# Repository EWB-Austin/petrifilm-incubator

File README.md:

# The Armadillo v1.0, a Low-cost, Portable, Petrifilm Incubator

The Armadillo v1.0 is a low-cost, portable Petrifilm(TM) Incubator for doing in-country bacterial analysis of water quality for Engineers Without Borders invented and engineered by the Instrumentation Group of [Great Austin Chapter](https://ewbgreateraustin.org/) of [EWB-USA](http://www.ewb-usa.org/).

Watch a 3-minute introductory [video](https://www.youtube.com/watch?v=0SzoYT8wLo0)!

The Armadillo won [1st place](https://ewbgreateraustin.org/2016/11/01/test/) in in the 2016 SCSE Regional Conference in Atlanta poster session contest.
As we like to say, "we beat NASA", with our [poster](https://github.com/EWB-Austin/petrifilm-incubator/blob/master/doc/EWBconferenceposterIncubator_handout_comp.pdf):

.

## Start Here: Documentation

We have a press release in progress which is not yet published.

Our [instructable](http://www.instructables.com/id/Portable-Petrifilm-Incubator-for-Inexpensive-In-Fi/)
gives step-by-step instructions for the construction of the Armadillo for about $160.

For those who prefer printable and sharable PDF, we have prepared a [construction manual](https://github.com/EWB-Austin/petrifilm-incubator/blob/master/doc/ConstructionManual.pdf).

Because the use of the Armadillo requires inoculating Petrifilms, we have prepared an
[inoculation manual](https://github.com/EWB-Austin/petrifilm-incubator/blob/master/doc/PetrifilmInoculation.pdf).

In the [experiments](https://github.com/EWB-Austin/petrifilm-incubator/tree/master/experiments) directory
you will find data from our battery-lifetime experiments.

## Status of the Project

We are:
* Preparing an academic paper with a plan to submit it to [Journal of Humanitarian Engineering](https://www.ewb.org.au/jhe/index.php/jhe).
* Planning some small improvements to create the Armadillo v2.0, such as the inclusion of a screwdriver and
a user manual in the Armadillo itself.
* Promoting the use and construction of the Aramadillo within EWB chapters.

## How You Can Help

We need someone to build an Armadillo!  Although we hope our published materials are self-sufficient,
we are happy to provide personal assistance and help in building your own Armadillo. We want to make
sure that our instruction materials are high-quality.

Please email: <a href="mailto: instrumentationmembers@ewbgreateraustin.org"> instrumentationmembers@ewbgreateraustin.org</a>  or visit our [chapter website](https://ewbgreateraustin.org/) to contact us.

## Older Documents

Our older README is [archived](https://github.com/EWB-Austin/petrifilm-incubator/2016-README.md).

## Contact

[Great Austin Chapter](https://ewbgreateraustin.org/) of [EWB-USA](http://www.ewb-usa.org/).
<a href="mailto: instrumentationmembers@ewbgreateraustin.org"> instrumentationmembers@ewbgreateraustin.org</a>

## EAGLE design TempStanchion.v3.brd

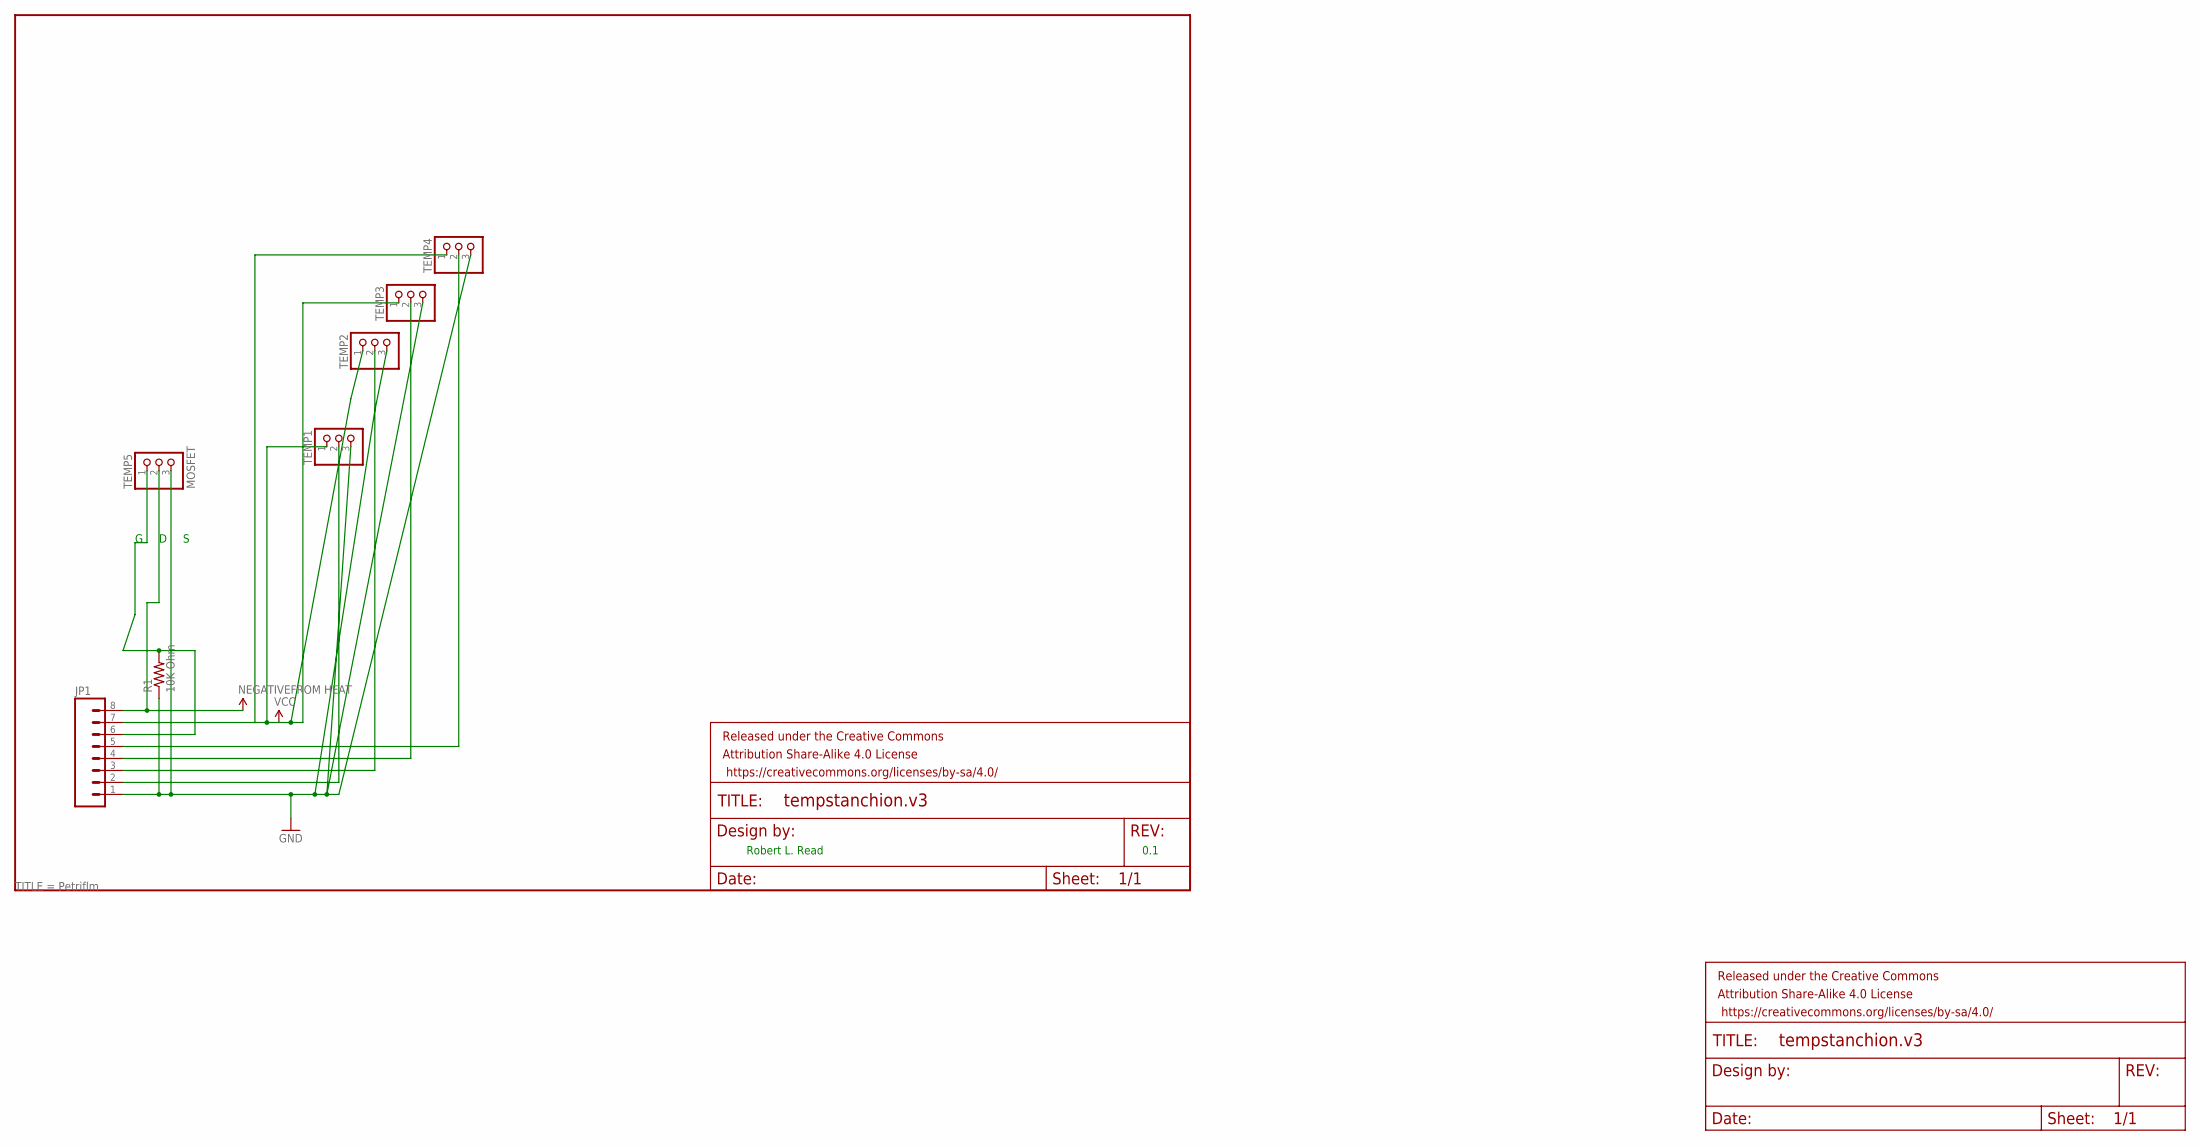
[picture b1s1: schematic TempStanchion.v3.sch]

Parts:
FRAME1, FRAME2: FRAME-LETTER; CREATIVE_COMMONS
JP1: M08; 1X08_ROUND
R1: 10K Ohm; AXIAL-0.6
TEMP1, TEMP2, TEMP3, TEMP4: PINHD-1X3; 1X03
TEMP5: MOSFET; 1X03

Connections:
GND: JP1.1, R1.P$1 (1), TEMP1.3, TEMP2.3, TEMP3.3, TEMP4.3, TEMP5.3
MOSFET: JP1.6, R1.P$2 (2), TEMP5.1
unnamed: JP1.2, TEMP1.2
unnamed: JP1.3, TEMP2.2
unnamed: JP1.4, TEMP3.2
unnamed: JP1.5, TEMP4.2
VCC: JP1.7, JP1.8, TEMP1.1, TEMP2.1, TEMP3.1, TEMP4.1, TEMP5.2

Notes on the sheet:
Robert L. Read
0.1

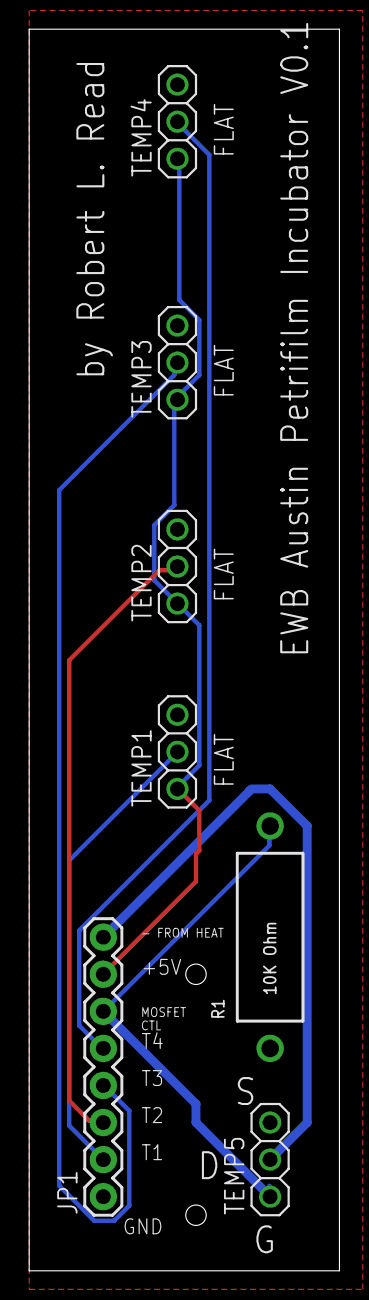
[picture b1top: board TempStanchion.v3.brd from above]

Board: 2 copper layers, 21.3 x 85.1 mm, 9 parts (0 on the bottom side), 7 nets.

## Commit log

2015-11-16 adding liquid crystal code
2015-11-16 adding diagram
2015-12-07 Adding latest version
2015-12-30 Adding first experiment
2016-01-25 Adding next experiment
2016-02-02 adding Eagle files for board
2016-02-07 latest file
2016-02-12 full experiment
2017-02-21 changing name
2017-02-21 create experiments directory
2017-02-21 organizing-data
2017-02-21 Initial Commit of Inoculation Instructions
2017-02-21 adding video
2017-02-21 addint video link
2017-02-27 updating README
2017-02-27 improved README;
2017-02-27 further improvements
2017-02-27 reorg and adding links
2017-02-27 adding
2017-02-27 trying to add image
2017-02-27 trying to get image to show up
2017-02-27 trying yet again
2017-02-27 once more...
2017-02-27 adding png
2017-02-27 improved links
2017-02-28 adding press release
2017-02-28 removing files
2017-02-28 update to construction manual
2017-03-21 Add files via upload
    Adding materials list and updating inoculation instructions
2017-03-21 adding a lot of photos (too mano many, maybe)
2017-03-23 adding Incubated Films
2017-09-06 some improvements in instructions
2018-03-02 adding UserGuide.pdf

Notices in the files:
parts and their libraries:
SparkFun-Connectors: Licensing: Creative Commons ShareAlike 4.0 International - https://creativecommons.org/licenses/by-sa/4.0
SparkFun-Aesthetics: Released under the Creative Commons Attribution Share-Alike 4.0 License
SparkFun-Aesthetics: https://creativecommons.org/licenses/by-sa/4.0
